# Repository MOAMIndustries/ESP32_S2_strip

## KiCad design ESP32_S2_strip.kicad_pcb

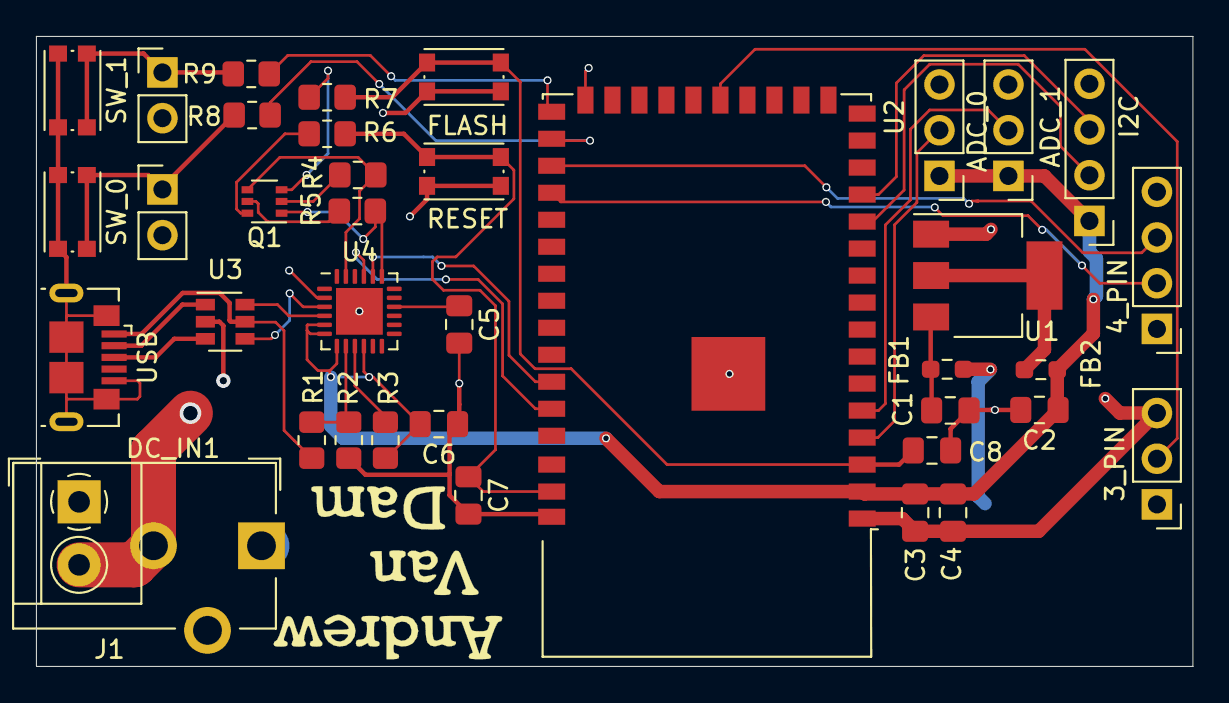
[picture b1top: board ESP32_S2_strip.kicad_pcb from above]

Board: 2 copper layers, 64.2 x 35.0 mm, 38 parts (0 on the bottom side), 34 nets.

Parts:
3_PIN: Conn_01x03_Male; PinHeader_1x03_P2.54mm_Vertical
4_PIN: Conn_01x04_Male; PinHeader_1x04_P2.54mm_Vertical
ADC_0, ADC_1: Conn_01x03_Male; PinHeader_1x03_P2.54mm_Vertical
C1, C4: 10uF; C_0805_2012Metric_Pad1.18x1.45mm_HandSolder
C2: 33uF; C_0805_2012Metric_Pad1.18x1.45mm_HandSolder
C3, C7, C8: 0.1uF; C_0805_2012Metric_Pad1.18x1.45mm_HandSolder
C5: 1uF; C_0805_2012Metric_Pad1.18x1.45mm_HandSolder
C6: C; C_0805_2012Metric_Pad1.18x1.45mm_HandSolder
DC_IN1: Screw_Terminal_01x02; TerminalBlock_4Ucon_1x02_P3.50mm_Horizontal
FB1, FB2: Ferrite_Bead_Small; R_0603_1608Metric_Pad0.98x0.95mm_HandSolder
FLASH: SW_Push; SW_Push_1P1T_NO_CK_KMR2
I2C: Conn_01x04_Male; PinHeader_1x04_P2.54mm_Vertical
J1: Barrel_Jack_Switch; BarrelJack_CUI_PJ-102AH_Horizontal
J3, J4: Conn_01x02_Male; PinHeader_1x02_P2.54mm_Vertical
Q1: MBT3904DW1; SOT-363_SC-70-6
R1: 24K; R_0805_2012Metric_Pad1.20x1.40mm_HandSolder
R2: 47K; R_0805_2012Metric_Pad1.20x1.40mm_HandSolder
R3, R8, R9: 1K; R_0805_2012Metric_Pad1.20x1.40mm_HandSolder
R4, R5: 10K; R_0805_2012Metric_Pad1.20x1.40mm_HandSolder
R6, R7: 0; R_0805_2012Metric_Pad1.20x1.40mm_HandSolder
RESET: SW_Push; SW_Push_1P1T_NO_CK_KMR2
SW_0, SW_1: SW_Push; SW_Push_1P1T_NO_CK_KMR2
U1: LM1117-3.3; SOT-223-3_TabPin2
U2: ESP32-S2-WROVER
U3: WE-TVS-82400102; SOT-23-6
U4: CP2104; QFN-24-1EP_4x4mm_P0.5mm_EP2.6x2.6mm
USB: USB_B_Micro; USB_Micro-B_GCT_USB3076-30-A

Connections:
+3V3: ADC_0.1, ADC_1.1, C2.1, C3.1, C4.1, C6.2, FB2.1, I2C.1, R3.2, U2.2, U4.5, U4.6, U4.7, U4.10
+5V: R1.2, U3.5, USB.1
/ESP32_USB_auto_reset/CHIP_PU: C7.1, R6.1, RESET.1, U2.41
/ESP32_USB_auto_reset/DTR: Q1.4, R4.2, U4.23
/ESP32_USB_auto_reset/GPIO0: C8.2, FLASH.1, R7.1, U2.3
/ESP32_USB_auto_reset/RTS: Q1.1, R5.2, U4.19
ADC0: ADC_0.2, U2.4
ADC1: ADC_1.2, U2.5
CLK: 4_PIN.2, U2.30
DATA: 4_PIN.3, U2.29
ESP32_RX: U2.38, U4.21
ESP32_TX: U2.37, U4.20
GND: 3_PIN.3, 4_PIN.4, ADC_0.3, ADC_1.3, C1.2, C2.2, C3.2, C4.2, C5.2, C6.1, C7.2, C8.1, DC_IN1.2, FLASH.2, I2C.4, J1.2, J3.2, J4.2, R2.2, RESET.2, SW_0.2, SW_1.2, U1.1, U2.1, U2.26, U2.42, U2.43, U3.2, U4.2, U4.25, USB.5, USB.6
I2C_CLK: I2C.2, U2.12
I2C_DATA: I2C.3, U2.13
unnamed: C1.1, FB1.1, U1.3
unnamed: C5.1, U4.16
unnamed: FB2.2, U1.2
unnamed: U3.1, USB.2
unnamed: U3.3, USB.3
unnamed: J3.1, R8.1, SW_0.1
unnamed: J4.1, R9.1, SW_1.1
unnamed: Q1.2, R4.1
unnamed: Q1.3, R7.2
unnamed: Q1.5, R5.1
unnamed: Q1.6, R6.2
unnamed: R1.1, R2.1, U4.8
unnamed: R3.1, U4.9
unnamed: R8.2, U2.28
unnamed: R9.2, U2.27
unnamed: U3.4, U4.3
unnamed: U3.6, U4.4
VCC: 3_PIN.1, 4_PIN.1, DC_IN1.1, FB1.2, J1.1
WS281x: 3_PIN.2, U2.21

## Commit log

2021-04-08 Basic ESP32 infrastructure
2021-04-08 Preliminary schematic capture
2021-04-08 semi schematiced
2021-04-09 Rev 1
